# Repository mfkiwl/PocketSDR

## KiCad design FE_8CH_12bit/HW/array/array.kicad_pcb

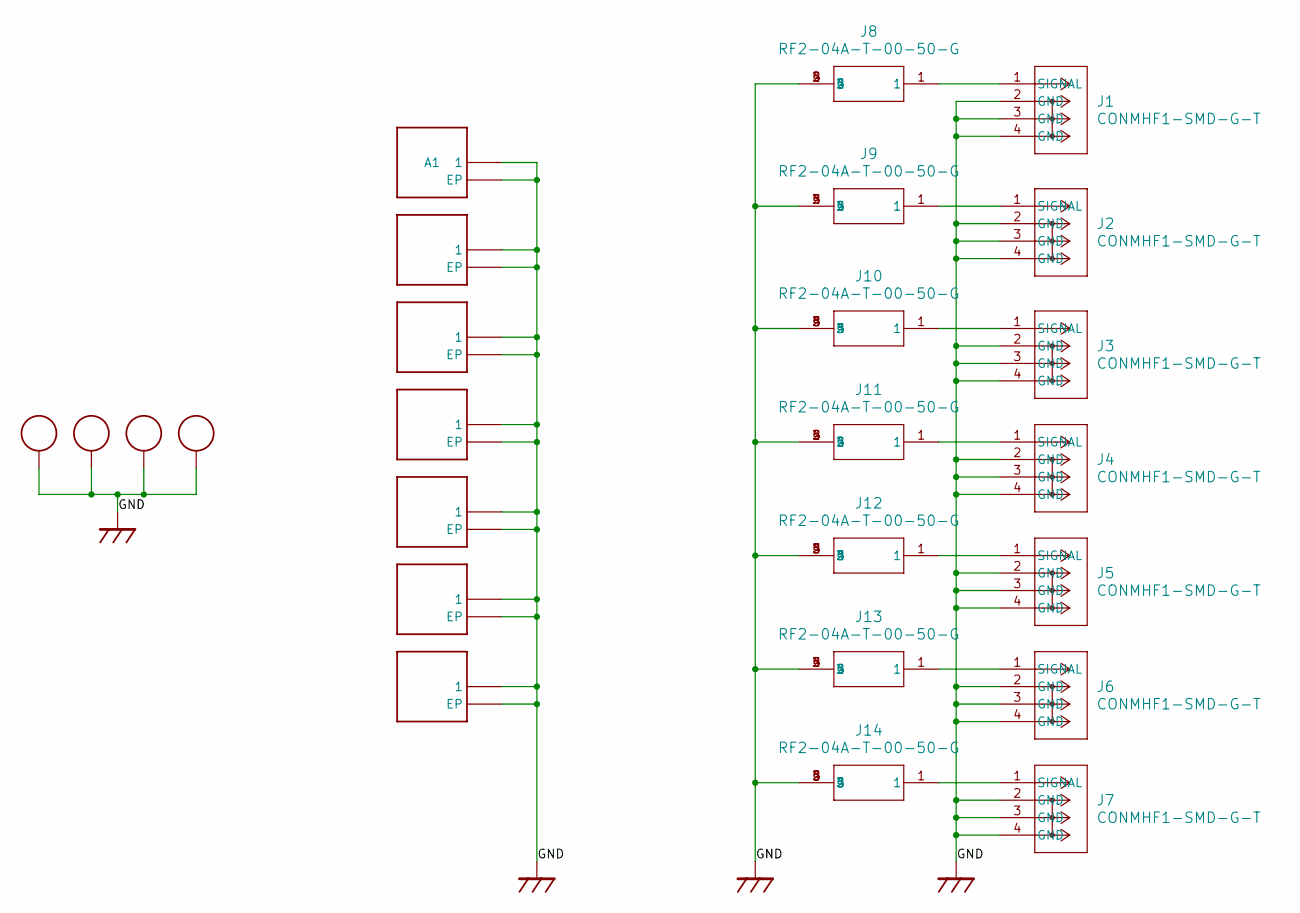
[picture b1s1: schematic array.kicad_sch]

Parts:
A1, A2, A3, A4, A5, A6, A7: ADFGP.25A
J1, J2, J3, J4, J5, J6, J7: CONMHF1-SMD-G-T; COAX3_CONMHF1-SMD-G-T_TEC
J8, J9, J10, J11, J12, J13, J14: RF2-04A-T-00-50-G; CONN_RF2-04A-T-00-50-G_ADM
PAD1, PAD2, PAD3, PAD4: CPAD_3.2MM

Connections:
/GND: A1.1, A1.EP, A2.1, A2.EP, A3.1, A3.EP, A4.1, A4.EP, A5.1, A5.EP, A6.1, A6.EP, A7.1, A7.EP, J1.2 (GND), J1.3 (GND), J1.4 (GND), J2.2 (GND), J2.3 (GND), J2.4 (GND), J3.2 (GND), J3.3 (GND), J3.4 (GND), J4.2 (GND), J4.3 (GND), J4.4 (GND), J5.2 (GND), J5.3 (GND), J5.4 (GND), J6.2 (GND), J6.3 (GND), J6.4 (GND), J7.2 (GND), J7.3 (GND), J7.4 (GND), J8.2, J8.3, J8.4, J8.5, J9.2, J9.3, J9.4, J9.5, J10.2, J10.3, J10.4, J10.5, J11.2, J11.3, J11.4, J11.5, J12.2, J12.3, J12.4, J12.5, J13.2, J13.3, J13.4, J13.5, J14.2, J14.3, J14.4, J14.5, PAD1.EP, PAD2.EP, PAD3.EP, PAD4.EP
unnamed: J1.1 (SIGNAL), J8.1
unnamed: J2.1 (SIGNAL), J9.1
unnamed: J3.1 (SIGNAL), J10.1
unnamed: J4.1 (SIGNAL), J11.1
unnamed: J5.1 (SIGNAL), J12.1
unnamed: J6.1 (SIGNAL), J13.1
unnamed: J7.1 (SIGNAL), J14.1

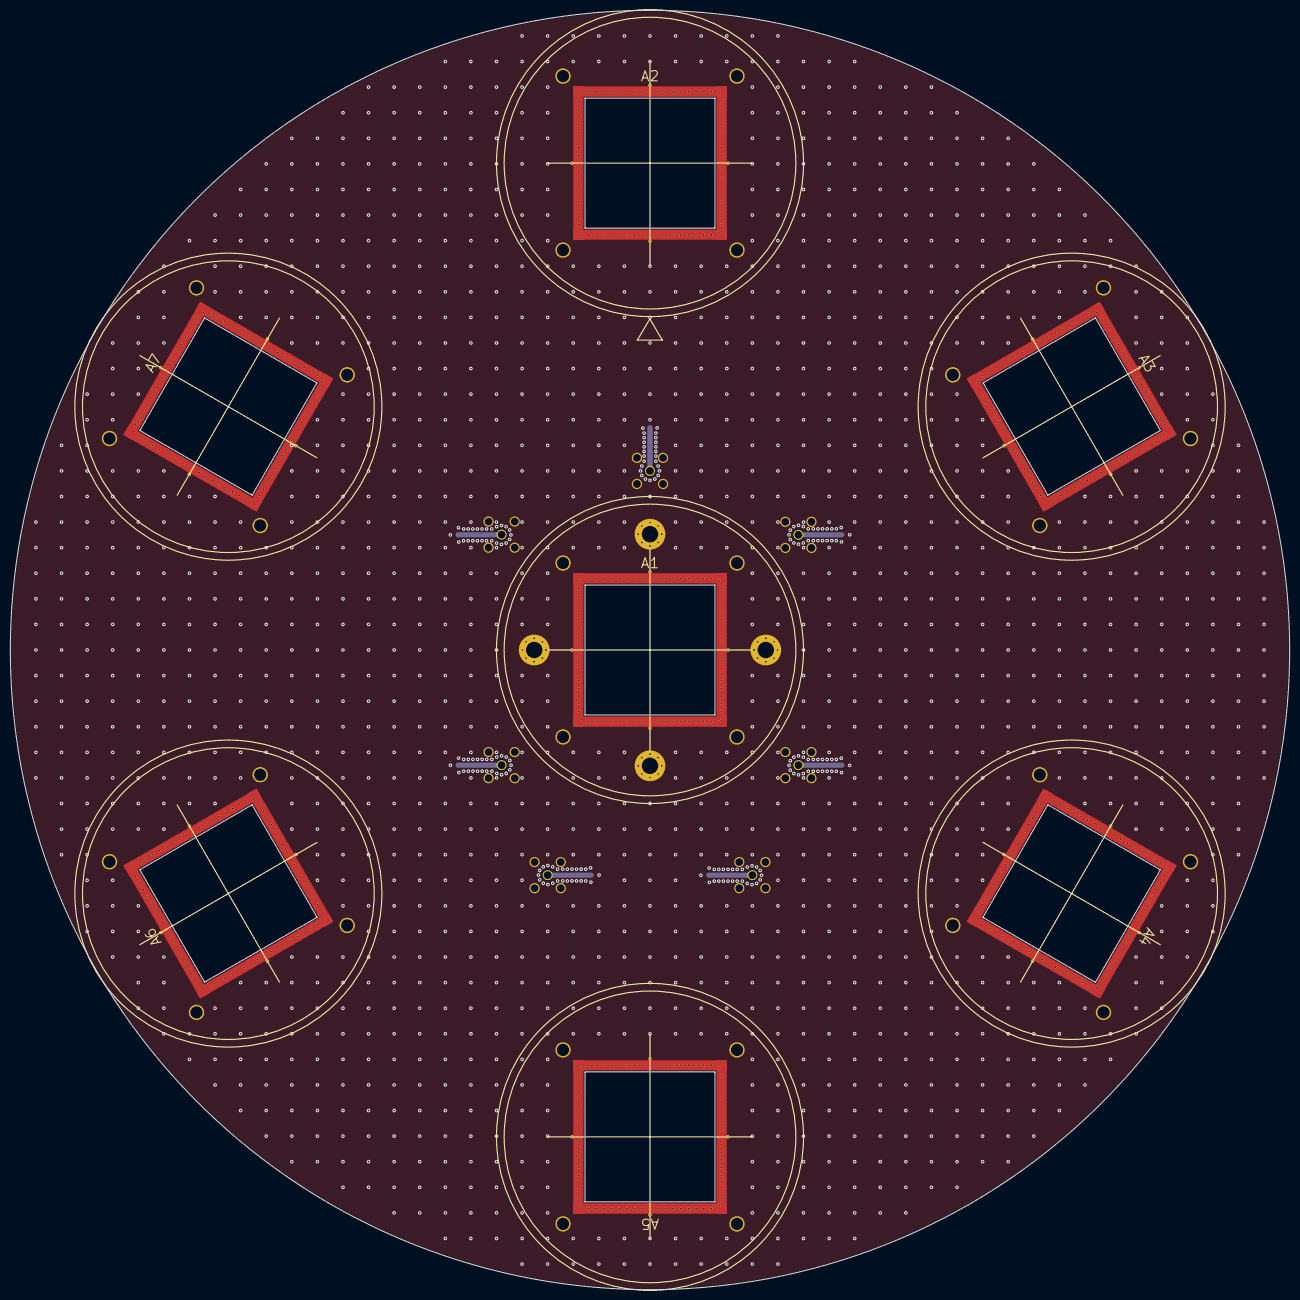
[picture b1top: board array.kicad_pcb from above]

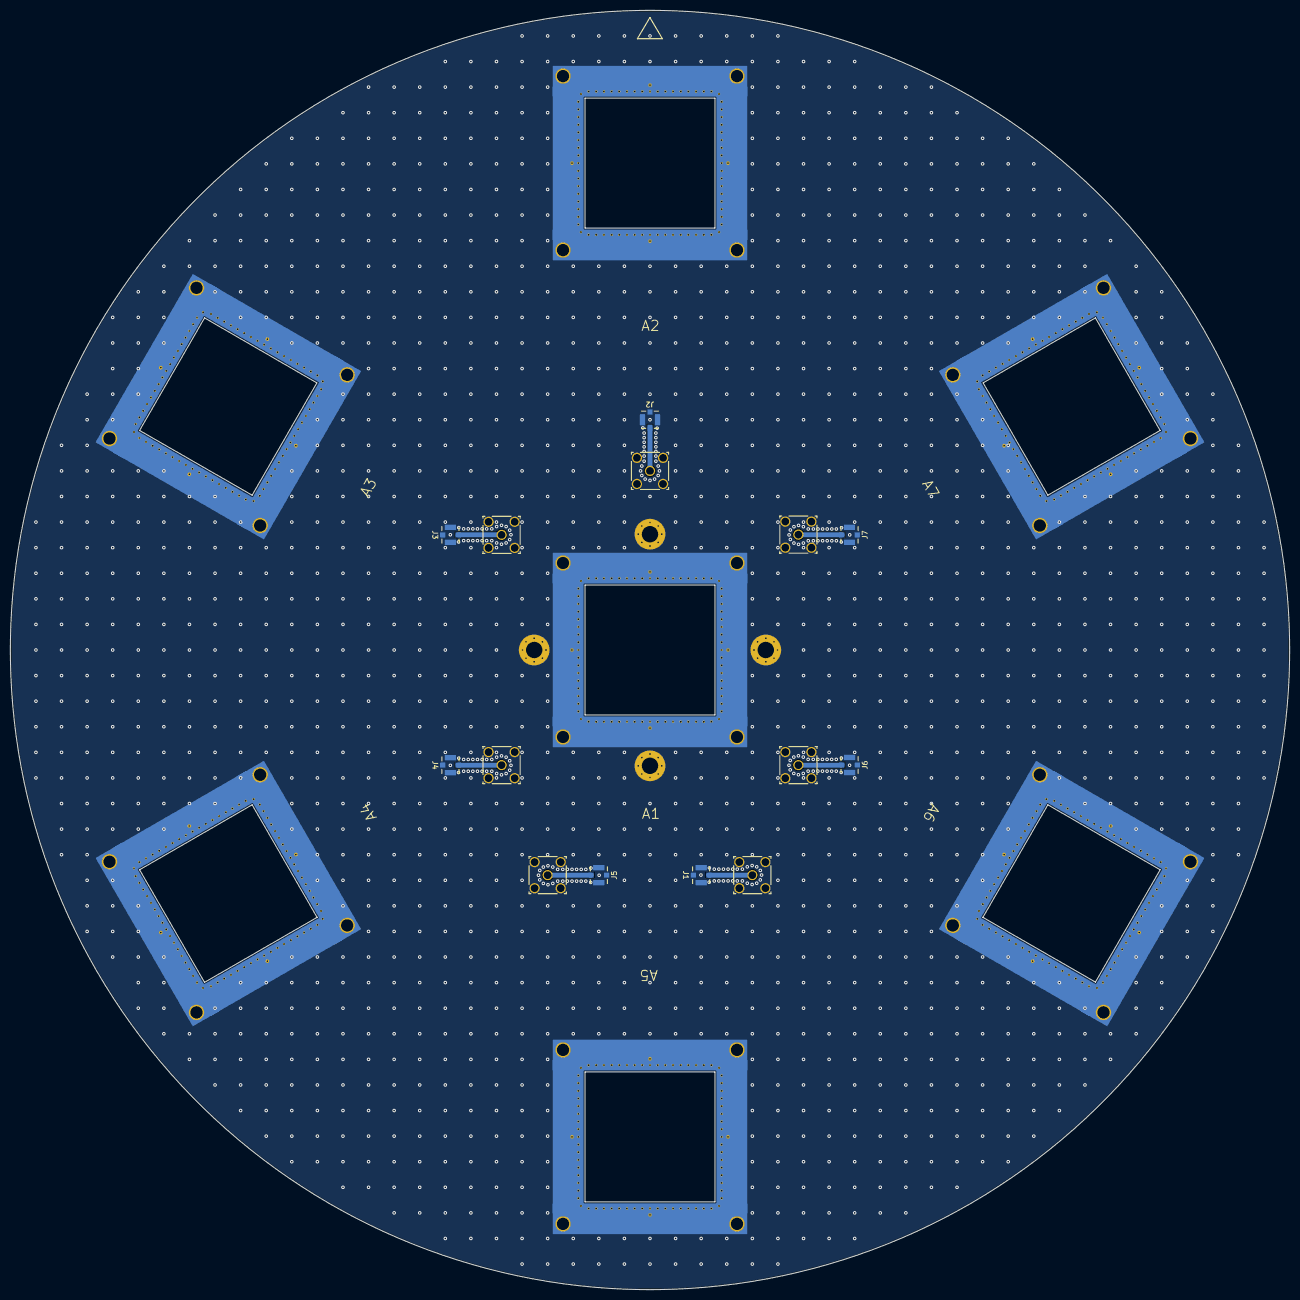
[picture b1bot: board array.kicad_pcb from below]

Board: 2 copper layers, 250.0 x 250.0 mm, 25 parts (14 on the bottom side), 8 nets.

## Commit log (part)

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2026-01-30 Added.
